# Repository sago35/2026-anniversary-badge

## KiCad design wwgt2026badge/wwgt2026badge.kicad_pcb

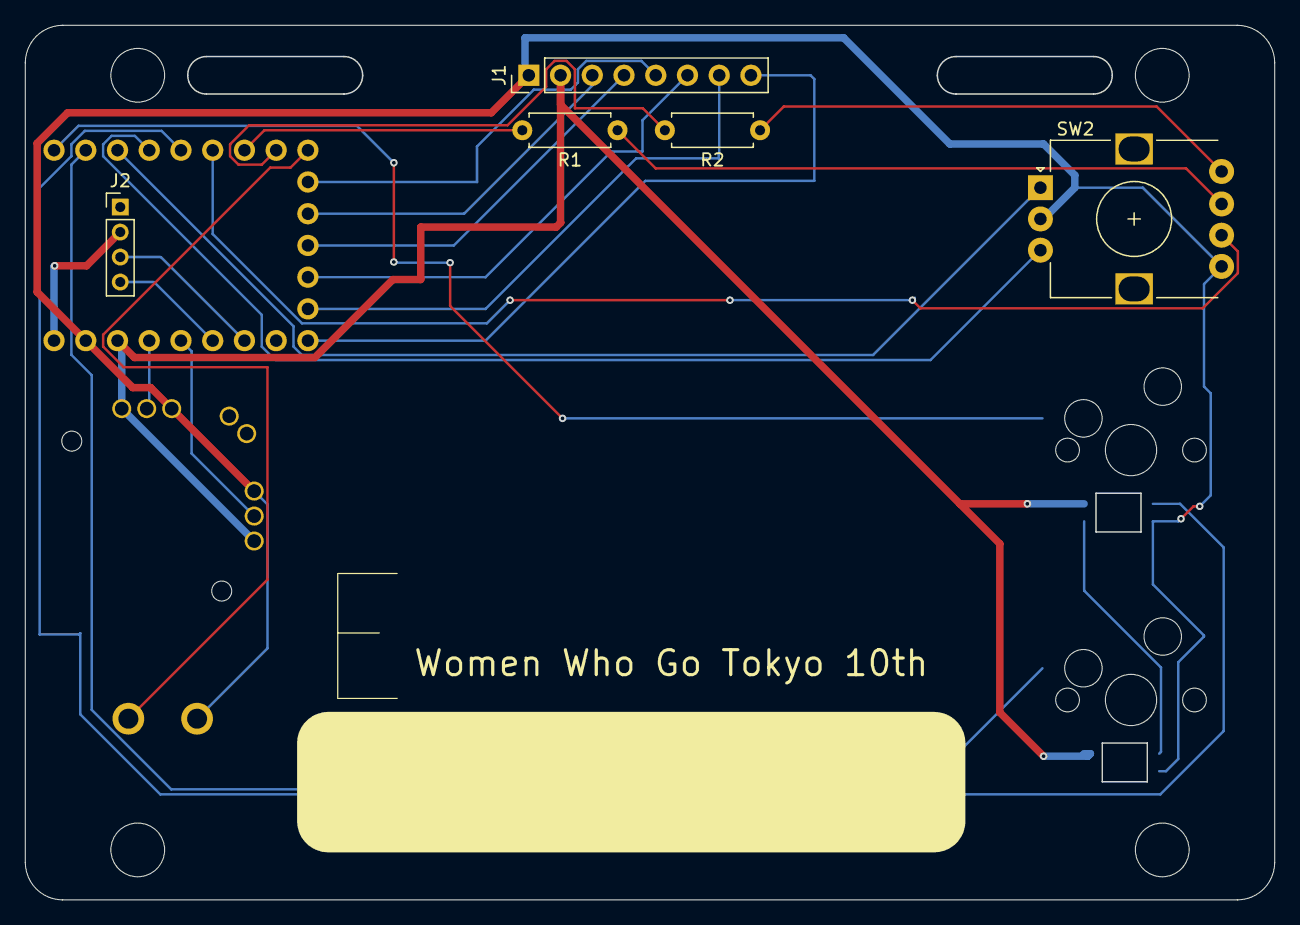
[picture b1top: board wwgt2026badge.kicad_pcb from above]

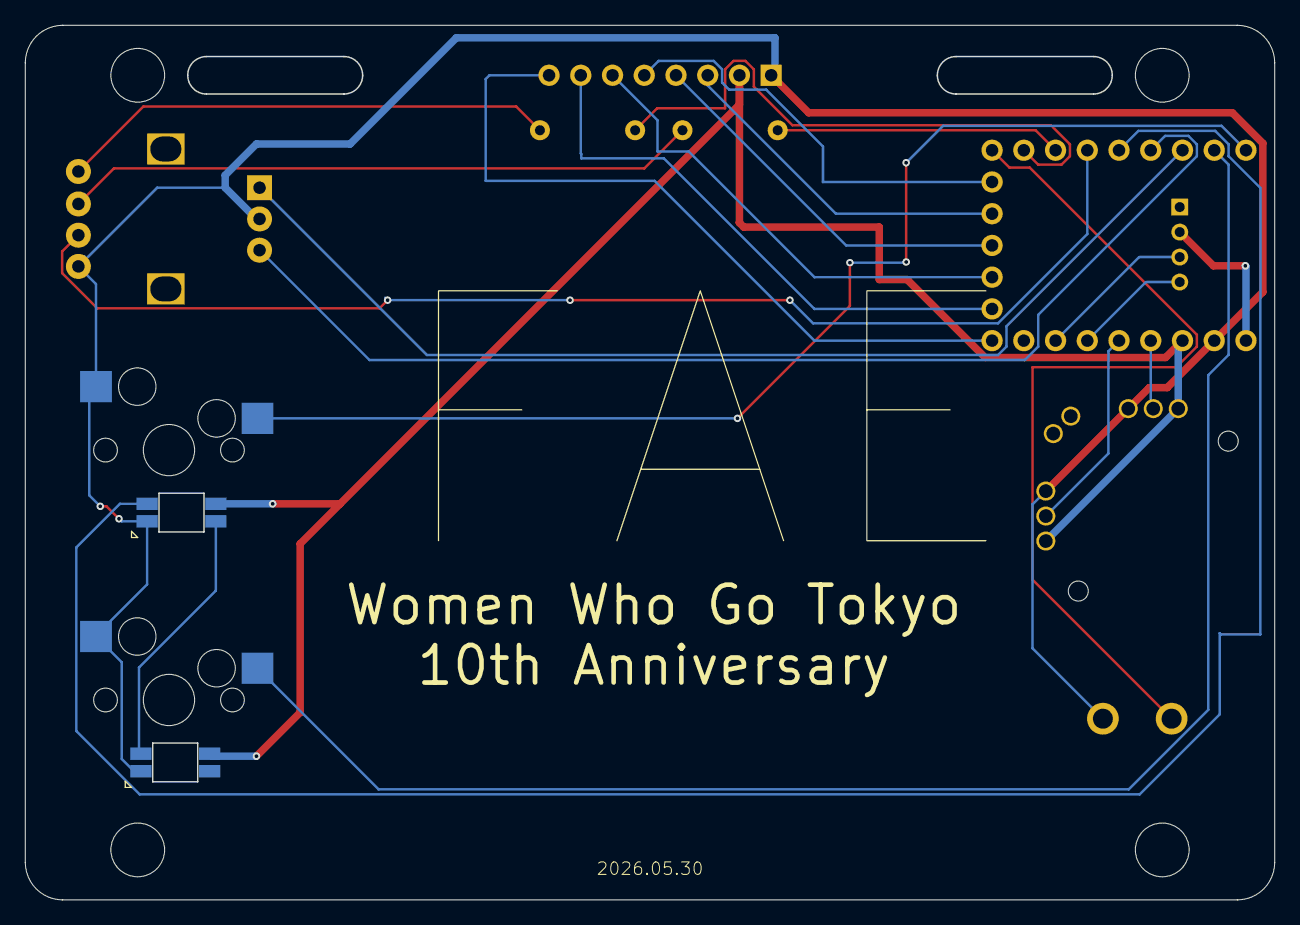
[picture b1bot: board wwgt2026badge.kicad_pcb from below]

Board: 2 copper layers, 100.0 x 70.0 mm, 18 parts (2 on the bottom side), 25 nets.

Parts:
BZ1: Buzzer; buzzer 5.5mm
H1, H2, H3, H4: MountingHole; M2_HOLE_v2
J1: Conn_01x08_Pin; PinHeader_1x08_P2.54mm_Vertical
J2: Conn_01x04_Pin; PinHeader_1x04_P2.00mm_Vertical
LED1, LED2: YS-SK6812MINI-E
R1, R2: R; R_Axial_DIN0207_L6.3mm_D2.5mm_P7.62mm_Horizontal
SW1, SW3: SW_PUSH; CherryMX_Hotswap
SW2, SW2#3: KEY_SWITCH; strap_hole
SW2#2: EC12PLGRSDVF; RotaryEncoder_Alps_EC12E-Switch_Vertical_H20mm_LED
U2: rp2040-zero
U3: fj08k-s; FJ08K-S

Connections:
3V3: J1.2, LED1.1 (VDD), LED2.1 (VDD), U2.21 (3V3), U3.3 (VR1-3), U3.4 (VR2-1)
/SCL1: J2.4, U2.18 (27)
/SDA1: J2.3, U2.17 (26)
BL: J1.8, U2.15 (14)
BUZZER: BZ1.1 (+), U2.9 (8)
CS: J1.7, U2.14 (13)
DC: J1.6, U2.13 (12)
ENC_BTN: SW2#2.2, U2.6 (5)
ENC_LED_1: R1.2, U2.7 (6)
ENC_LED_2: R2.2, U2.8 (7)
GND: BZ1.2 (-), J1.1, J2.1, LED1.3 (VSS), LED2.3 (VSS), SW1.2, SW2#2.1, SW2#2.C, SW3.2, U2.22 (GND), U3.1 (VR1-1), U3.6 (VR2-3)
unnamed: LED1.2 (DOUT), LED2.4 (DIN)
unnamed: R1.1, SW2#2.3
unnamed: R2.1, SW2#2.4
RES: J1.5, U2.10 (9)
ROT_A: SW2#2.A, U2.3 (2)
ROT_B: SW2#2.B, U2.4 (3)
SCL: J1.3, U2.11 (10)
SDA: J1.4, U2.12 (11)
SK6812MINI-E: LED1.4 (DIN), U2.5 (4)
SW_1: SW1.1, U2.2 (1)
SW_2: SW3.1, U2.1 (0)
VCC: J2.2, U2.23 (5V)
VR_X: U2.20 (29), U3.2 (VR1-2)
VR_Y: U2.19 (28), U3.5 (VR2-2)

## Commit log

2026-04-05 設定を調整
2026-04-05 おそらく不要である conf2025badge_lib.pretty を削除
2026-04-05 PIN 名を更新
